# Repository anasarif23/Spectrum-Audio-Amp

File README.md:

## Version 0

The first version of the schematic, completed while learning KiCad fundamentals. This version has some design mistakes that I identified during review, including [add specifics if you can — e.g. incorrect regulator pinout, missing decoupling capacitors, etc.]. I used Claude as a learning resource throughout this stage to understand regulator behavior, KiCad's schematic tools, and best practices for power supply design.

📄 See `Advanced Audio Amplifier Schematic.pdf` for the full Version 0 schematic.

## Version 1

A revised, cleaner version of the schematic with the Version 0 mistakes corrected and the overall layout better organized. This version is still in progress — the schematic is further along, and I'm now working on completing the full PCB layout.

🖼️ See `Audio Amplifier Version 1.png` for the current schematic.

## Version 2

The PCB layout stage — all components have been placed on the board. Routing has not started yet; that's the next step.

📄 See `Audio_Amplifier.pdf` for the schematic and `Audio_Amplifier PCB FULL LAYOUT.pdf` for the current component placement.

🖼️ See `Audio_Amplifier 3D-PIC.png` for a 3D render of the board as placed so far.

---

## Bill of Materials (from schematic)

### Active Components

| Ref | Part | Description |
|-----|------|--------------|
| U1, U6–U13 | NE5532 | Dual op-amp — used across the pre-amp stage and the 7 gyrator filter bands |
| U2 | LM317-TO220 | Adjustable positive linear regulator |
| U3 | LM337-TO220 | Adjustable negative linear regulator |
| U4 | LM2596S-5 | Switching buck regulator (5V rail) |
| U5 | LMC835N | Graphic equalizer IC |
| U14 | MSGEQ7 | 7-band spectrum analyzer IC |
| U15 | Teensy 4.1 | Microcontroller |
| U16 | SN74AHCT125N | Quad buffer / 3.3V logic level shifter |
| U18 | PAM8403D | Class-D speaker amplifier |
| PS1 | DCWN03A-12 | Isolated DC-DC converter |
| D1 | 1N5822 | Schottky diode |
| D2–D9 | LED | Status/indicator LEDs |
| SW1–SW7 | Rotary Encoder | 7-band control knobs |
| RV1 | 10k | Potentiometer |
| L1 | 33µH | Inductor (buck regulator) |
| FB1 | Ferrite Bead | EMI suppression |
| J1 | SJ-3523-SMT | Audio input jack |
| J2 | Barrel Jack | 12V power input |
| J3, J4 | Screw_Terminal_01x02 | Power/output connections |
| J6 | Conn_01x06 | Pin header |

### Passives

Roughly 96 resistors (R1–R96) and 110 capacitors (C1–C110) make up the gyrator filter networks (tuned for the 63Hz–16kHz bands), op-amp gain/bias networks, and decoupling/filtering throughout the board. Full reference-designator values are in the schematic (`Audio_Amplifier.pdf`).

---

## Status

🚧 **In progress** — schematic complete (Version 1); PCB component placement complete (Version 2), routing still to be done.

## Tools Used

- KiCad (schematic capture, PCB layout)
- NE5532 dual op-amps (pre-amp and gyrator filter stages)
- LM317 / LM337 adjustable linear regulators, LM2596S-5 switching regulator
- MSGEQ7 spectrum analyzer IC, LMC835N graphic equalizer IC
- Teensy 4.1 microcontroller
- PAM8403D class-D amplifier

## What I Learned

Iterating between Version 0 and Version 1 taught me to catch design errors early through review rather than discovering them at the prototyping stage — a habit I now apply to every new project. I also used Claude as a learning tool throughout this project to fill gaps in my coursework, particularly around regulator dropout behavior and KiCad workflow, then applied that understanding directly to my design decisions.

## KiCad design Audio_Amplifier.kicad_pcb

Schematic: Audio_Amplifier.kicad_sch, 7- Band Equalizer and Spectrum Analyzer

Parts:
C1, C2: 2.2uF; CP_Radial_D7.5mm_P2.50mm
C3, C6, C16, C17, C51, C54, C88, C89, C90, C109, C110: 1uF; CP_Radial_D6.3mm_P2.50mm
C4, C5, C15, C18, C63, C64, C91: 0.1uF; CP_Radial_D6.3mm_P2.50mm
C7: 220uF; CP_Radial_D7.5mm_P2.50mm
C8, C10, C11, C14, C43, C46, C48, C50, C57, C58, C61, C62, C65, C66, C69, C70, C73, C74, C79, C80, C84, C87: 100nF; C_Disc_D3.0mm_W1.6mm_P2.50mm
C9: 220uF; CP_Radial_D6.3mm_P2.50mm
C12, C13, C44, C45, C47, C49, C52, C55, C56, C59, C60, C67, C68, C71, C72, C76, C77, C78, C81, C82, C83, C86: 10uF; CP_Radial_D6.3mm_P2.50mm
C19, C94, C107: 0.47uF; CP_Radial_D6.3mm_P2.50mm
C20, C22: 0.033uF; C_Disc_D3.0mm_W1.6mm_P2.50mm
C21: 0.47uF; C_Disc_D3.0mm_W1.6mm_P2.50mm
C23, C25: 0.15uF; C_Disc_D3.0mm_W1.6mm_P2.50mm
C24, C26: 0.015uF; C_Disc_D3.0mm_W1.6mm_P2.50mm
C27, C29: 0.068uF; C_Disc_D3.0mm_W1.6mm_P2.50mm
C28, C30: 0.0068uF; C_Disc_D3.0mm_W1.6mm_P2.50mm
C31, C33: 0.022uF; C_Disc_D3.0mm_W1.6mm_P2.50mm
C32, C34: 0.0033uF; C_Disc_D3.0mm_W1.6mm_P2.50mm
C35, C37: 0.01uF; C_Disc_D3.0mm_W1.6mm_P2.50mm
C36, C38: 0.0015uF; C_Disc_D3.0mm_W1.6mm_P2.50mm
C39, C41: 0.0047uF; C_Disc_D3.0mm_W1.6mm_P2.50mm
C40, C42, C53, C75: 680pF; C_Disc_D3.0mm_W1.6mm_P2.50mm
C85: 33pF; C_Disc_D3.0mm_W1.6mm_P2.50mm
C92, C93, C95, C96, C97, C98, C99, C100, C101, C102, C103, C104, C105, C106: 10nF; C_Disc_D3.0mm_W1.6mm_P2.50mm
C108: 470uF; CP_Radial_D6.3mm_P2.50mm
D1: 1N5822; D_DO-201AD_P15.24mm_Horizontal
D2, D3, D4, D5, D6, D7, D8, D9: LED; LED_D5.0mm
FB1: FerriteBead; LairdTech_28C0236-0JW-10
J1: SJ-3523-SMT; Jack_3.5mm_CUI_SJ-3523-SMT_Horizontal
J2: Barrel_Jack; BarrelJack_GCT_DCJ200-10-A_Horizontal
J3, J4: Screw_Terminal_01x02; TerminalBlock_CUI_TB007-508-02_1x02_P5.08mm_Horizontal
J6: Conn_01x06_Pin; PinHeader_1x06_P1.00mm_Vertical
L1: 33uH; L_Radial_D8.7mm_P5.00mm_Fastron_07HCP
PS1: DCWN03A-12; DCWN03A12; Mouser Part Number 709-DCWN03A-12
R1, R2, R3, R50, R53: 47k; R_Axial_DIN0204_L3.6mm_D1.6mm_P5.08mm_Horizontal
R4, R10: 22k; R_Axial_DIN0204_L3.6mm_D1.6mm_P5.08mm_Horizontal
R5, R6, R57, R62: 100; R_Axial_DIN0204_L3.6mm_D1.6mm_P5.08mm_Horizontal
R7, R8: 1.8k; R_Axial_DIN0204_L3.6mm_D1.6mm_P5.08mm_Horizontal
R9, R13: 240; R_Axial_DIN0204_L3.6mm_D1.6mm_P5.08mm_Horizontal
R11, R12: 1.2k; R_Axial_DIN0204_L3.6mm_D1.6mm_P5.08mm_Horizontal
R14, R16, R17, R18, R20, R21, R23, R24, R26, R27, R29, R30, R33, R36, R39, R42, R45, R48, R51, R54, R56, R61, R64, R67, R68, R74: 100k; R_Axial_DIN0204_L3.6mm_D1.6mm_P5.08mm_Horizontal
R15, R19, R22, R25, R28, R31, R34, R37, R40, R43, R46, R49, R52, R55: 680; R_Axial_DIN0204_L3.6mm_D1.6mm_P5.08mm_Horizontal
R32, R35, R38, R41: 82k; R_Axial_DIN0204_L3.6mm_D1.6mm_P5.08mm_Horizontal
R44, R47: 62k; R_Axial_DIN0204_L3.6mm_D1.6mm_P5.08mm_Horizontal
R58, R60, R63, R66: 470; R_Axial_DIN0204_L3.6mm_D1.6mm_P5.08mm_Horizontal
R59, R65: 6.8k; R_Axial_DIN0204_L3.6mm_D1.6mm_P5.08mm_Horizontal
R69: 200k; R_Axial_DIN0204_L3.6mm_D1.6mm_P5.08mm_Horizontal
R70, R71, R72, R73, R75, R76, R78, R79, R80, R81, R82, R83, R84, R85, R86, R87, R88, R89, R95, R96: 10k; R_Axial_DIN0204_L3.6mm_D1.6mm_P5.08mm_Horizontal
R77: 2.2k; R_Axial_DIN0204_L3.6mm_D1.6mm_P5.08mm_Horizontal
R90, R91, R92, R93, R94: 1.5k; R_Axial_DIN0204_L3.6mm_D1.6mm_P5.08mm_Horizontal
RV1: 10k; POT_PDB182_BRN
SW1, SW2, SW3, SW4, SW5, SW6, SW7: RotaryEncoder; RotaryEncoder_Alps_EC11E_Vertical_H20mm
U1, U6, U7, U8, U9, U10, U11, U12, U13: NE5532; DIP-8_W7.62mm
U2: LM317_TO-220; TO-220-3_Vertical
U3: LM337_TO220; TO-220-3_Vertical
U4: LM2596S-5; TO-263-5_TabPin3
U5: LMC835N; DIP-28_W15.24mm
U14: MSGEQ7; SOIC-8_3.9x4.9mm_P1.27mm
U15: Teensy4.1; Teensy41
U16: SN74AHCT125N; DIP-14_W7.62mm
U18: PAM8403D; SOIC-16_3.9x9.9mm_P1.27mm

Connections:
/+3.3V: C83.1, C84.1, R69.2, R75.2, R76.2, R78.2, R79.2, R80.2, R81.2, R82.2, R83.2, R84.2, R85.2, R86.2, R87.2, R88.2, R89.2, U14.1 (VDD), U15.46 (3V3)
/+5V: C9.1, C10.1, C63.1, C64.1, C86.2, C87.1, C88.1, C89.1, C90.1, C108.1, J6.5, L1.2, R72.1, R73.1, R94.1, U4.4 (FB), U15.48 (VIN), U16.12 (4A), U16.14 (VCC), U18.4 (PVDD), U18.6 (VDD), U18.13 (PVDD)
/+7.5V: C3.2, C13.2, C14.2, C43.1, C44.2, C47.2, C48.1, C55.2, C57.1, C59.2, C61.1, C65.1, C67.2, C69.1, C71.2, C73.1, C77.1, C79.1, C81.2, R9.1, R91.2, U1.8 (V+), U2.2 (VO), U5.17 (VDD), U6.8 (V+), U7.8 (V+), U8.8 (V+), U9.8 (V+), U10.8 (V+), U11.8 (V+), U12.8 (V+), U13.8 (V+)
/+12V: C7.1, C8.1, J2.1, PS1.22 (+VIN_1), PS1.23 (+VIN_2), R77.2, U4.1 (VIN)
/+12V_ISO: C4.2, PS1.14 (+VOUT), R92.1, U2.3 (VI)
/-7.5V: C6.1, C11.2, C12.2, C45.2, C46.1, C49.2, C50.1, C56.2, C58.1, C60.2, C62.1, C66.1, C68.2, C70.1, C72.2, C74.1, C78.1, C80.1, C82.2, R13.1, R90.2, U1.4 (V-), U3.3 (VO), U5.12 (VSS), U6.4 (V-), U7.4 (V-), U8.4 (V-), U9.4 (V-), U10.4 (V-), U11.4 (V-), U12.4 (V-), U13.4 (V-)
/-12V_ISO: C5.1, PS1.11 (-VOUT), R93.1, U3.2 (VI)
/ATTEN_ RAW_L_AUDIO: RV1.5, U1.5 (+)
/ATTEN_ RAW_R_AUDIO: RV1.2, U1.3 (+)
/Band1A: C92.2, R75.1, SW1.A, U15.28 (36_CS)
/Band1B: C93.2, R76.1, SW1.B, U15.29 (37_CS)
/Band2A: C96.2, R79.1, SW2.A, U15.30 (38_CS1_IN1)
/Band2B: C95.2, R78.1, SW2.B, U15.31 (39_MISO1_OUT1A)
/Band3A: C98.2, R81.1, SW3.A, U15.32 (40_A16)
/Band3B: C97.2, R80.1, SW3.B, U15.33 (41_A17)
/Band4A: C105.2, R88.1, SW4.A, U15.35 (13_SCK_LED)
/Band4B: C106.2, R89.1, SW4.B, U15.36 (14_A0_TX3_SPDIF_OUT)
/Band5A: C104.2, R87.1, SW5.A, U15.37 (15_A1_RX3_SPDIF_IN)
/Band5B: C103.2, R86.1, SW5.B, U15.38 (16_A2_RX4_SCL1)
/Band6A: C101.2, R84.1, SW6.A, U15.39 (17_A3_TX4_SDA1)
/Band6B: C102.2, R85.1, SW6.B, U15.40 (18_A4_SDA)
/Band7A: C100.2, R83.1, SW7.A, U15.41 (19_A5_SCL)
/Band7B: C99.2, R82.1, SW7.B, U15.20 (28_RX7)
/EQ_CLK: U5.14 (CLK), U16.3 (1Y)
/EQ_CLK_3.3V: U15.4 (2_OUT2), U16.2 (1A)
/EQ_DATA: U5.16 (DATA), U16.8 (3Y)
/EQ_DATA_3.3V: U15.6 (4_BCLK2), U16.9 (3A)
/EQ_OUT_L: C52.1, C94.1, R61.2, R68.2
/EQ_OUT_R: C76.1, C107.1, R67.2, R74.2
/EQ_STROBE: U5.15 (STROBE), U16.6 (2Y)
/EQ_STROBE_3.3V: U15.5 (3_LRCLK2), U16.5 (2A)
/LC1: C16.2, R16.1, U5.5 (LC1)
/LC2: C19.2, R21.1, U5.6 (LC2)
/LC3: C23.2, R27.1, U5.7 (LC3)
/LC4: C27.2, R33.1, U5.8 (LC4)
/LC5: C31.2, R39.1, U5.9 (LC5)
/LC6: C35.2, R45.1, U5.10 (LC6)
/LC7: C39.2, R51.1, U5.11 (LC7)
/LC8: C17.2, R18.1, U5.24 (LC8)
/LC9: C21.2, R24.1, U5.23 (LC9)
/LC10: C25.2, R30.1, U5.22 (LC10)
/LC11: C29.2, R36.1, U5.21 (LC11)
/LC12: C33.2, R42.1, U5.20 (LC12)
/LC13: C37.2, R48.1, U5.19 (LC13)
/LC14: C41.2, R54.1, U5.18 (LC14)
/L_EQ_SUM: R15.2, R16.2, R21.2, R22.2, R27.2, R28.2, R33.2, R34.2, R39.2, R40.2, R45.2, R46.2, R51.2, R52.2, R57.2, U5.2 (AIN2), U6.1, U6.2 (-), U7.1, U7.2 (-), U8.1, U8.2 (-), U9.1, U9.2 (-), U10.1, U10.2 (-), U11.1, U11.2 (-), U12.1, U12.2 (-)
/MSGEQ7_OUT: U14.3 (OUT), U15.42 (20_A6_TX5_LRCLK1)
/MSGEQ7_RESET: U14.7 (RESET), U15.12 (10_CS_MQSR)
/MSGEQ7_STROBE: U14.4 (STROBE), U15.11 (9_OUT1C)
/PRE_AMP_L: R6.1, U5.1 (AIN1)
/PRE_AMP_R: R5.1, U5.3 (AIN3)
/RAW_LEFT_AUDIO: C1.1, R8.2
/RAW_RIGHT_AUDIO: C2.1, R7.2
/R_EQ_SUM: R18.2, R19.2, R24.2, R25.2, R30.2, R31.2, R36.2, R37.2, R42.2, R43.2, R48.2, R49.2, R54.2, R55.2, R62.2, U5.27 (AIN5), U6.6 (-), U6.7, U7.6 (-), U7.7, U8.6 (-), U8.7, U9.6 (-), U9.7, U10.6 (-), U10.7, U11.6 (-), U11.7, U12.6 (-), U12.7
/SPKR_LN: J3.2, U18.3 (LOUT-)
/SPKR_LP: J3.1, U18.1 (LOUT+)
/SPKR_RN: J4.1, U18.14 (ROUT-)
/SPKR_RP: J4.2, U18.16 (ROUT+)
/TFT_CS: J6.1, U15.16 (24_A10_TX6_SCL2)
/TFT_DC: J6.2, U15.3 (1_TX1_CTX2_MISO1)
/TFT_MOSI: J6.3, U15.26 (34_RX8)
/TFT_SCK: J6.4, U15.27 (35_TX8)
AGND: C3.1, C4.1, C5.2, C6.2, C13.1, C14.1, C43.2, C44.1, C45.1, C46.2, C47.1, C48.2, C49.1, C50.2, C55.1, C56.1, C57.2, C58.2, C59.1, C60.1, C61.2, C62.2, C65.2, C66.2, C67.1, C68.1, C69.2, C70.2, C71.1, C72.1, C73.2, C74.2, C77.2, C78.2, C79.2, C80.2, C81.1, C82.1, C85.2, C88.2, C89.2, C90.2, C91.2, C108.2, C109.2, C110.2, D3.2 (A), D4.1 (K), D5.1 (K), D6.2 (A), D8.1 (K), D9.1 (K), FB1.1, J1.1, PS1.9 (COMMON_1), PS1.16 (COMMON_2), R1.2, R2.2, R3.2, R11.2, R12.1, R14.1, R17.1, R20.1, R23.1, R26.1, R29.1, R32.1, R35.1, R38.1, R41.1, R44.1, R47.1, R50.1, R53.1, R56.1, R60.2, R61.1, R63.2, R64.1, R67.1, RV1.3, RV1.6, U5.28 (A.GND), U14.2 (VSS), U14.6 (GND), U18.2 (PGND), U18.11 (GND), U18.15 (PGND)
DGND: C7.2, C8.2, C9.2, C10.2, C11.1, C12.1, C63.2, C64.2, C83.2, C84.2, C86.1, C87.2, C92.1, C93.1, C95.1, C96.1, C97.1, C98.1, C99.1, C100.1, C101.1, C102.1, C103.1, C104.1, C105.1, C106.1, D1.2 (A), D2.1 (K), D7.1 (K), FB1.2, J2.2, J6.6, PS1.2 (-VIN_1), PS1.3 (-VIN_2), SW1.C, SW2.C, SW3.C, SW4.C, SW5.C, SW6.C, SW7.C, U4.3 (GND), U4.5 (~ON/OFF), U5.13 (D.GND), U15.1 (GND), U15.34 (GND), U15.52 (GND), U15.58 (GND), U15.59 (GND), U16.1 (*1OE), U16.4 (*2OE), U16.7 (GND), U16.10 (*3OE), U16.13 (*4OE)
unnamed: C1.2, J1.2
unnamed: C2.2, J1.3
unnamed: C15.2, C16.1, R15.1
unnamed: C17.1, C18.2, R19.1
unnamed: C19.1, C20.2, R22.1
unnamed: C21.1, C22.2, R25.1
unnamed: C23.1, C24.2, R28.1
unnamed: C25.1, C26.2, R31.1
unnamed: C27.1, C28.2, R34.1
unnamed: C29.1, C30.2, R37.1
unnamed: C31.1, C32.2, R40.1
unnamed: C33.1, C34.2, R43.1
unnamed: C35.1, C36.2, R46.1
unnamed: C37.1, C38.2, R49.1
unnamed: C39.1, C40.2, R52.1
unnamed: C41.1, C42.2, R55.1
unnamed: C51.2, R57.1
unnamed: C52.2, R58.1
unnamed: C53.1, R58.2, R59.1, U13.1
unnamed: C54.2, R62.1
unnamed: C75.1, R65.1, R66.2, U13.7
unnamed: C76.2, R66.1
unnamed: C94.2, R70.1
unnamed: C107.2, R71.1
unnamed: D1.1 (K), L1.1, U4.2 (OUT)
unnamed: D2.2 (A), R77.1
unnamed: D3.1 (K), R90.1
unnamed: D4.2 (A), R91.1
unnamed: D5.2 (A), R92.2
unnamed: D6.1 (K), R93.2
unnamed: D7.2 (A), R94.2
unnamed: D8.2 (A), R95.1
unnamed: D9.2 (A), R96.1
unnamed: R4.1, R5.2, U1.1
unnamed: R7.1, RV1.1
unnamed: R8.1, RV1.4
unnamed: R6.2, R10.1, U1.7
unnamed: R4.2, U1.2 (-)
unnamed: R10.2, U1.6 (-)
unnamed: C109.1, R9.2, R11.1, U2.1 (ADJ)
unnamed: C110.1, R12.2, R13.2, U3.1 (ADJ)
unnamed: R1.1, U5.4 (AIN4)
unnamed: R2.1, U5.26 (AIN6)
unnamed: R3.1, U5.25 (AIN7)
unnamed: C15.1, R14.2, U6.3 (+)
unnamed: C18.1, R17.2, U6.5 (+)
unnamed: C20.1, R20.2, U7.3 (+)
unnamed: C22.1, R23.2, U7.5 (+)
unnamed: C24.1, R26.2, U8.3 (+)
unnamed: C26.1, R29.2, U8.5 (+)
unnamed: C28.1, R32.2, U9.3 (+)
unnamed: C30.1, R35.2, U9.5 (+)
unnamed: C32.1, R38.2, U10.3 (+)
unnamed: C34.1, R41.2, U10.5 (+)
unnamed: C36.1, R44.2, U11.3 (+)
unnamed: C38.1, R47.2, U11.5 (+)
unnamed: C40.1, R50.2, U12.3 (+)
unnamed: C42.1, R53.2, U12.5 (+)
unnamed: C51.1, R56.2, U13.3 (+)
unnamed: C53.2, R59.2, R60.1, U13.2 (-)
unnamed: C54.1, R64.2, U13.5 (+)
unnamed: C75.2, R63.1, R65.2, U13.6 (-)
unnamed: C85.1, R69.1, U14.8 (CKIN)
unnamed: R68.1, R74.1, U14.5 (IN)
unnamed: R70.2, U18.7 (INL)
unnamed: R71.2, U18.10 (INR)
unnamed: C91.1, U18.8 (VREF)
unnamed: R73.2, R95.2, U18.5 (~MUTE)
unnamed: R72.2, R96.2, U18.12 (~SHDN)

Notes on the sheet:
TFT_SCREEN
63Hz
7-Band Control
2.5KHz
Power
400Hz
160Hz
16KHz
LMC835N
Gyrators(63Hz - 16Khz)
6.3KHz
ATTENUATED AUDIO SIGNAL
Pre-Amp Stage
1KHz
LOGIC LEVEL SHIFTER 3.3V
MSGEQ7
SPEAKER AMP
TEENSY 4.1 (Microcontroller)

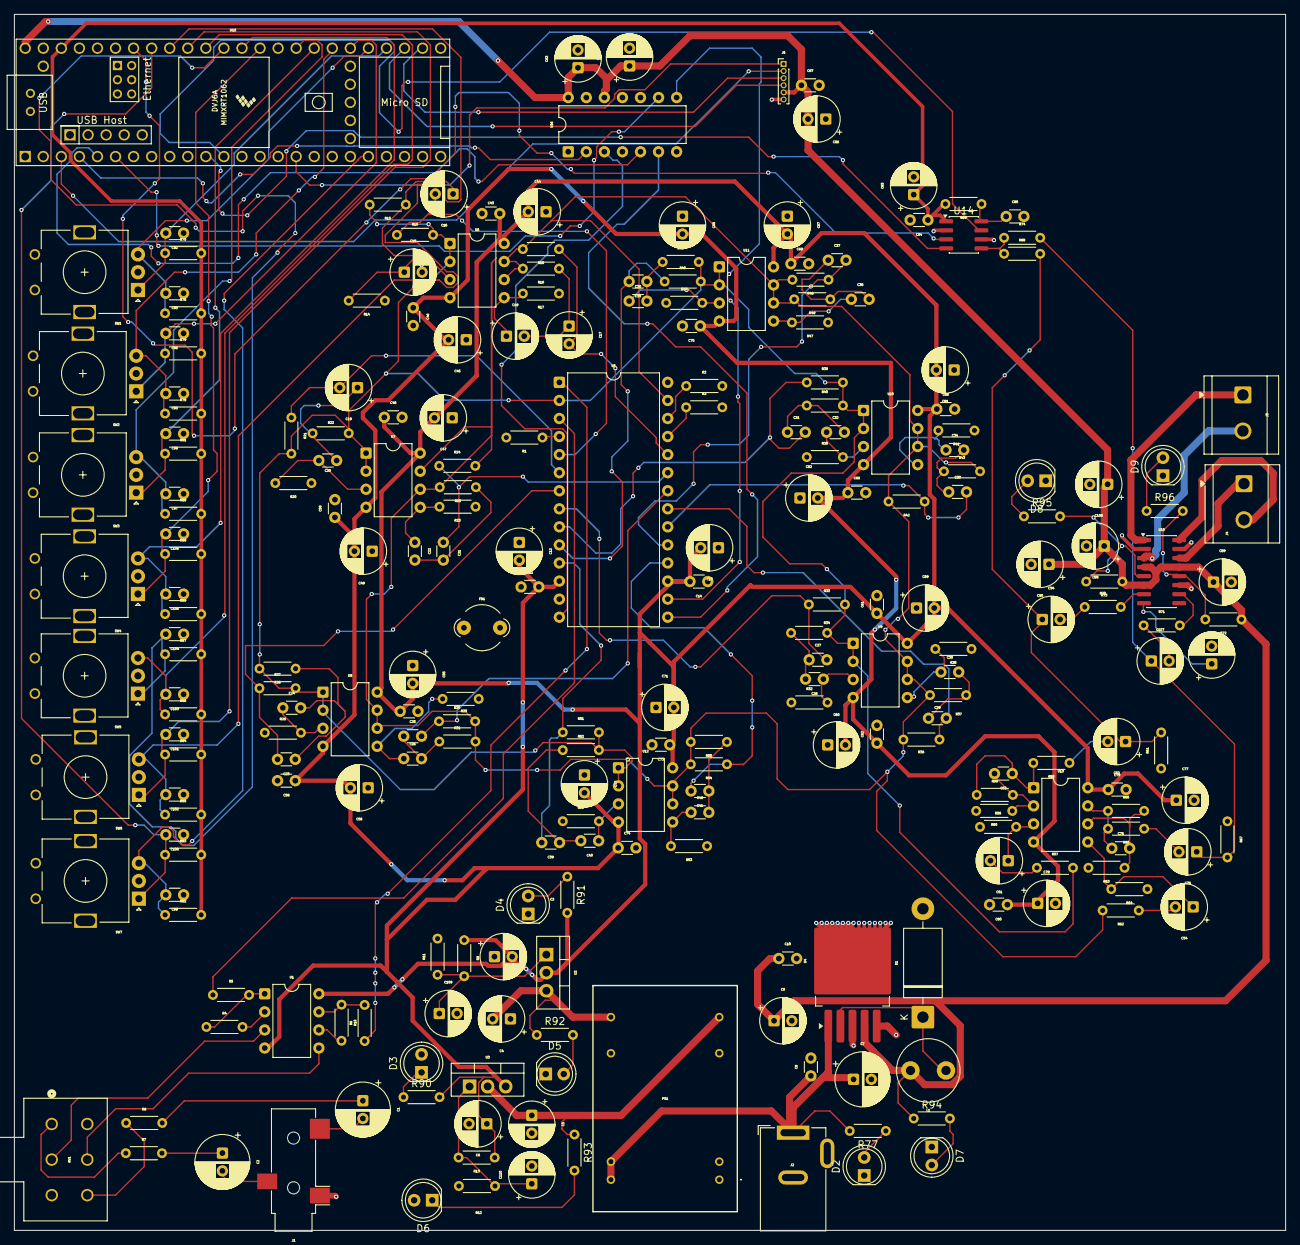
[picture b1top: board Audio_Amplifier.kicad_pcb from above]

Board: 4 copper layers, 178.8 x 171.0 mm, 248 parts (0 on the bottom side), 133 nets.
